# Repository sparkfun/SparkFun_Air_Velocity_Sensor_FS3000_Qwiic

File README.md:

SparkFun Air Velocity Sensor Breakout - FS3000 (Qwiic)
========================================

<table class="table table-hover table-striped table-bordered">
  <tr align="center">
   <td></td>
   <td></td>
  </tr>
  <tr align="center">
   <td><i>SparkFun Air Velocity Sensor Breakout <br /> FS3000-1005 (Qwiic) <br /> [ <a href="https://www.sparkfun.com/products/18377">SEN-18377</a> ]</i></td>
   <td><i>SparkFun Air Velocity Sensor Breakout <br /> FS3000-1015 (Qwiic) <br /> [ <a href="https://www.sparkfun.com/products/18768">SEN-18768</a> ]</i></td>
  </tr>
</table>

The SparkFun Air Velocity Sensor Breakout - FS3000 (Qwiic) makes it easy to use the Renesas FS3000 module. The FS3000 is a surface-mount type air velocity module utilizing a MEMS thermopile-based sensor. The FS3000 features a digital output with 12-bit resolution. The sensor comprises a "solid" thermal isolation technology and siliconcarbide coating to protect it from abrasive wear and water condensation. The FS3000 features a compact design fit for low profile enclosures.

There are two versions of this sensor with different upper ranges (1005/1015). This SparkFun product breaks out both versions on separate breakout boards: the 1005 version which can sense 0-7.23m/s (0-16.17mph) and 1015 version which can sense 0-15m/s (0-33.6mph).

SparkFun labored with love to create this code. Feel like supporting open source hardware?
Buy a [board](https://www.sparkfun.com/products/18377) or [two](https://www.sparkfun.com/products/18768) from SparkFun!

Repository Contents
-------------------

* **/Hardware** - Eagle design files (.brd, .sch)
* **/Hardware/Production** - Production panel files (.brd)
* **/Documents** - Datasheet, dimensional drawings.

Documentation
--------------

* **[Installing an Arduino Library Guide](https://learn.sparkfun.com/tutorials/installing-an-arduino-library)** - Basic information on how to install an Arduino library.
* **[Arduino Library](https://github.com/sparkfun/SparkFun_FS3000_Arduino_Library)** - Arduino Library for the Air Velocity Sensor FS3000.
* **[Hookup Guide](https://learn.sparkfun.com/tutorials/air-velocity-sensor-breakout---fs3000-hookup-guide)** - Hookup guide for the SparkFun Qwiic Air Velocity Sensor - FS3000.

Product Versions
----------------
* [SEN-18768](https://www.sparkfun.com/products/18768) - v1.0 with FS3000-1015
* [SEN-18377](https://www.sparkfun.com/products/18377) - v1.0 with FS3000-1005, Initial Release

License Information
-------------------

This product is _**open source**_! 

Please review the LICENSE.md file for license information. 

If you have any questions or concerns on licensing, please contact technical support on our [SparkFun forums](https://forum.sparkfun.com/viewforum.php?f=152).

Distributed as-is; no warranty is given.

- Your friends at SparkFun.

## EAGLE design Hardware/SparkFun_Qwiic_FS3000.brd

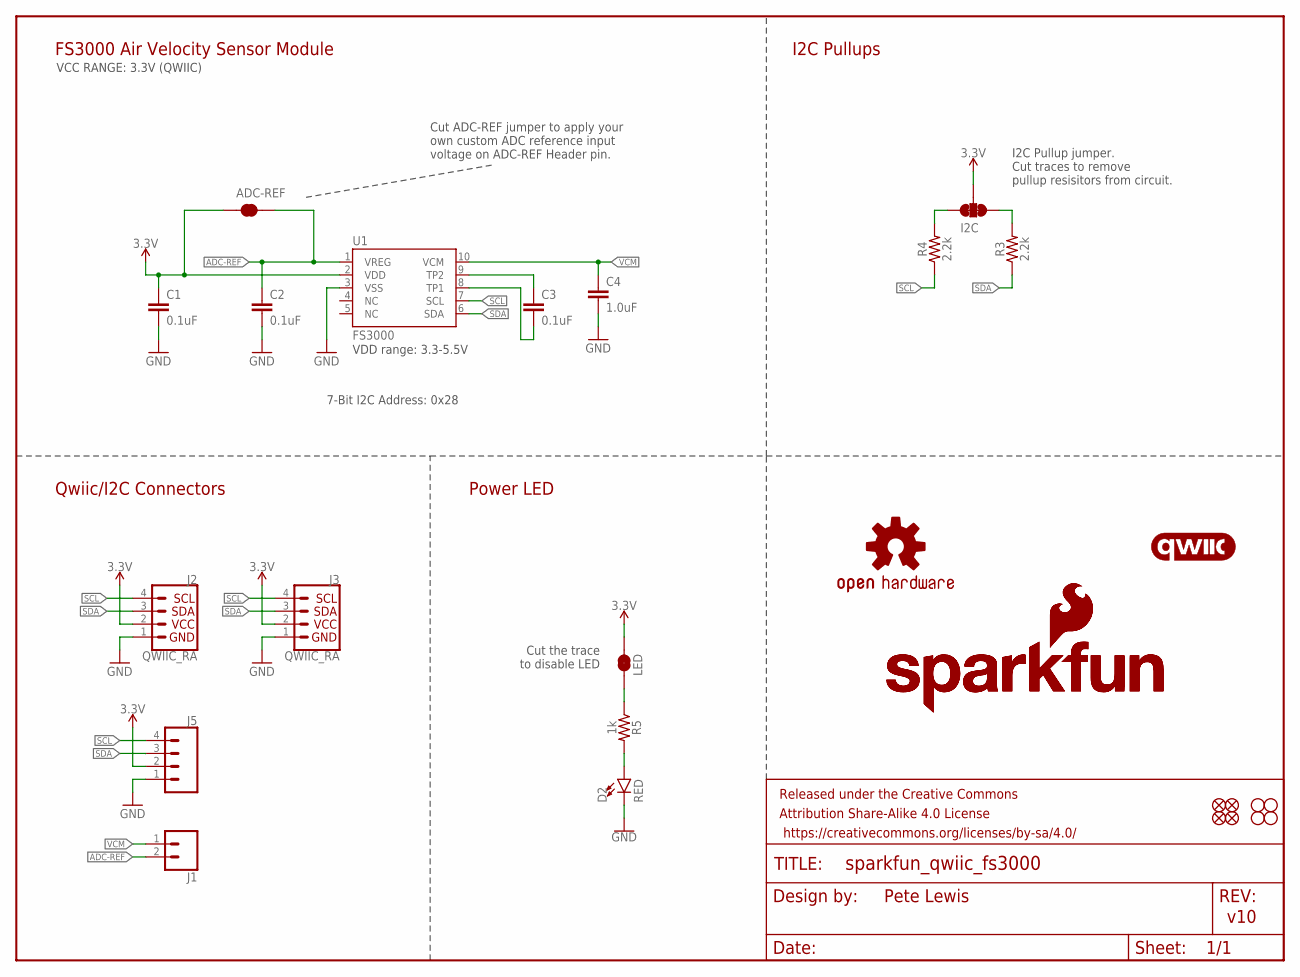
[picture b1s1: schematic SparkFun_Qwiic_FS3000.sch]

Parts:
ADC-REF: JUMPER-SMT_2_NC_TRACE_SILK; SMT-JUMPER_2_NC_TRACE_SILK
C1, C2, C3: 0.1uF; 0402-TIGHT
C4: 1.0uF; 0402-TIGHT
D2: RED; LED-0603
FRAME1: FRAME-LETTER; CREATIVE_COMMONS
I2C: JUMPER-SMT_3_2-NC_TRACE_SILK; SMT-JUMPER_3_2-NC_TRACE_SILK
J1: CONN_021X02_NO_SILK; 1X02_NO_SILK
J2, J3: QWIIC_RA; JST04_1MM_RA
J5: CONN_041X04_NO_SILK; 1X04_NO_SILK
JP1: LED; SMT-JUMPER_2_NC_TRACE_SILK
JP2, JP5, JP6, JP11: FIDUCIALUFIDUCIAL; FIDUCIAL-MICRO
JP3, JP4, JP7, JP8: STAND-OFF
LOGO1: OSHW-LOGOMINI; OSHW-LOGO-MINI
LOGO3, LOGO5: SFE_LOGO_NAME_FLAME.1_INCH; SFE_LOGO_NAME_FLAME_.1
LOGO4: QWIIC_LOGO_5MM; QWIIC_5MM
R3, R4: 2.2k; 0402-TIGHT
R5: 1k; 0402-TIGHT
U1: FS3000

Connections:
3.3V: ADC-REF.1, C1.1, I2C.2, J2.2, J3.2, J5.2, JP1.2, U1.2 (VDD)
ADC-REF: ADC-REF.2, C2.1, J1.2, U1.1 (VREG)
GND: C1.2, C2.2, C4.2, D2.C, J2.1, J3.1, J5.1, U1.3 (VSS)
unnamed: I2C.1, R3.2
unnamed: I2C.3, R4.2
unnamed: C3.1, U1.9 (TP2)
unnamed: C3.2, U1.8 (TP1)
unnamed: D2.A, R5.2
unnamed: JP1.1, R5.1
SCL: J2.4, J3.4, J5.4, R4.1, U1.7 (SCL)
SDA: J2.3, J3.3, J5.3, R3.1, U1.6 (SDA)
VCM: C4.1, J1.1, U1.10 (VCM)

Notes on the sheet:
7-Bit I2C Address: 0x28
Pete Lewis
v10
FS3000 Air Velocity Sensor Module
Qwiic/I2C Connectors
I2C Pullup jumper. Cut traces to remove pullup resisitors from circuit.
Cut the trace to disable LED
Power LED
VCC RANGE: 3.3V (QWIIC)
I2C Pullups
Cut ADC-REF jumper to apply your own custom ADC reference input voltage on ADC-REF Header pin.
VDD range: 3.3-5.5V

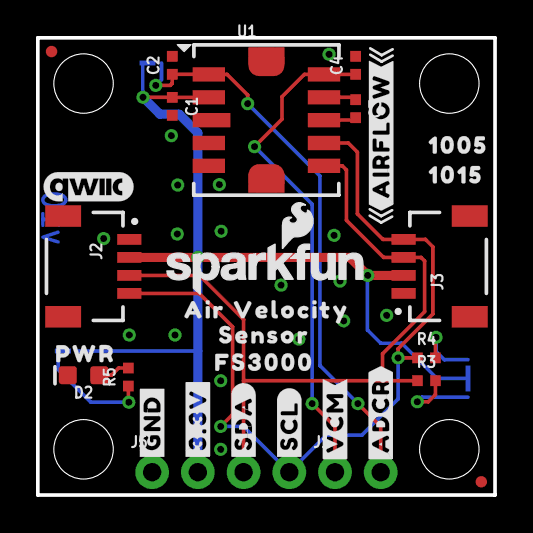
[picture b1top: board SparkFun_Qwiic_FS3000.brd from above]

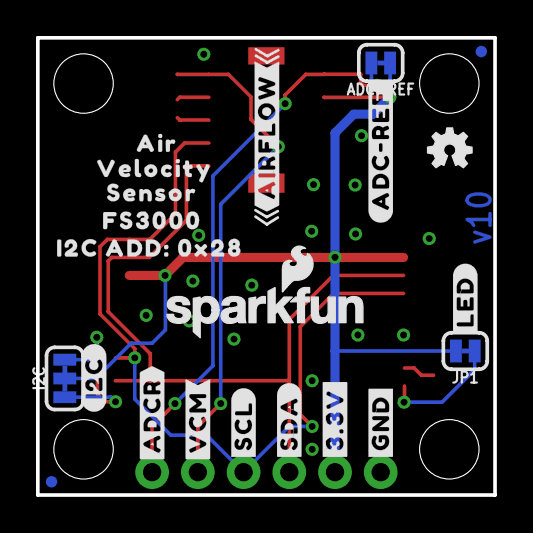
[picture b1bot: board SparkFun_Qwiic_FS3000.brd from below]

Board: 2 copper layers, 25.4 x 25.4 mm, 58 parts (22 on the bottom side), 12 nets.

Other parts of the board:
U$3, U$11: #SCL#0
U$4, U$9: #SDA#0
U$5, U$6: #GND#0
U$7, U$8: #3#3V#0
U$10, U$13: #ADCR#4
U$12: 10050
U$14, U$17: FS30001
U$15: #ADC#REF#0
U$16, U$20: VELOCITY30003
U$18, U$21: AIR30004
U$19, U$22: SENSOR30005
U$23, U$26: #AIRFLOW#0
U$24: #LED#0
U$25: PWR0
U$27: #I2C#0
U$28: I2C_ADD#_0X280
U$29: 10150
U$30, U$31: #VCM#3

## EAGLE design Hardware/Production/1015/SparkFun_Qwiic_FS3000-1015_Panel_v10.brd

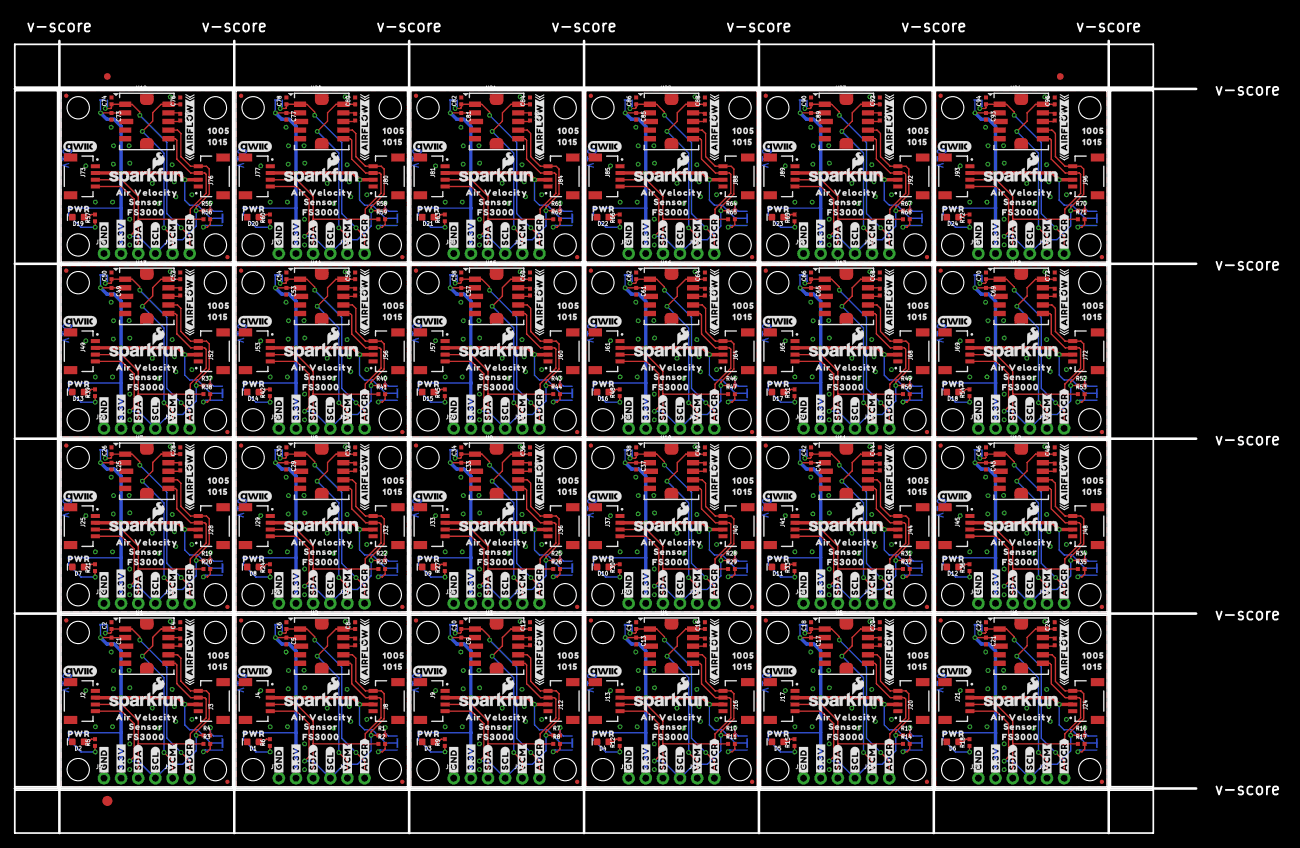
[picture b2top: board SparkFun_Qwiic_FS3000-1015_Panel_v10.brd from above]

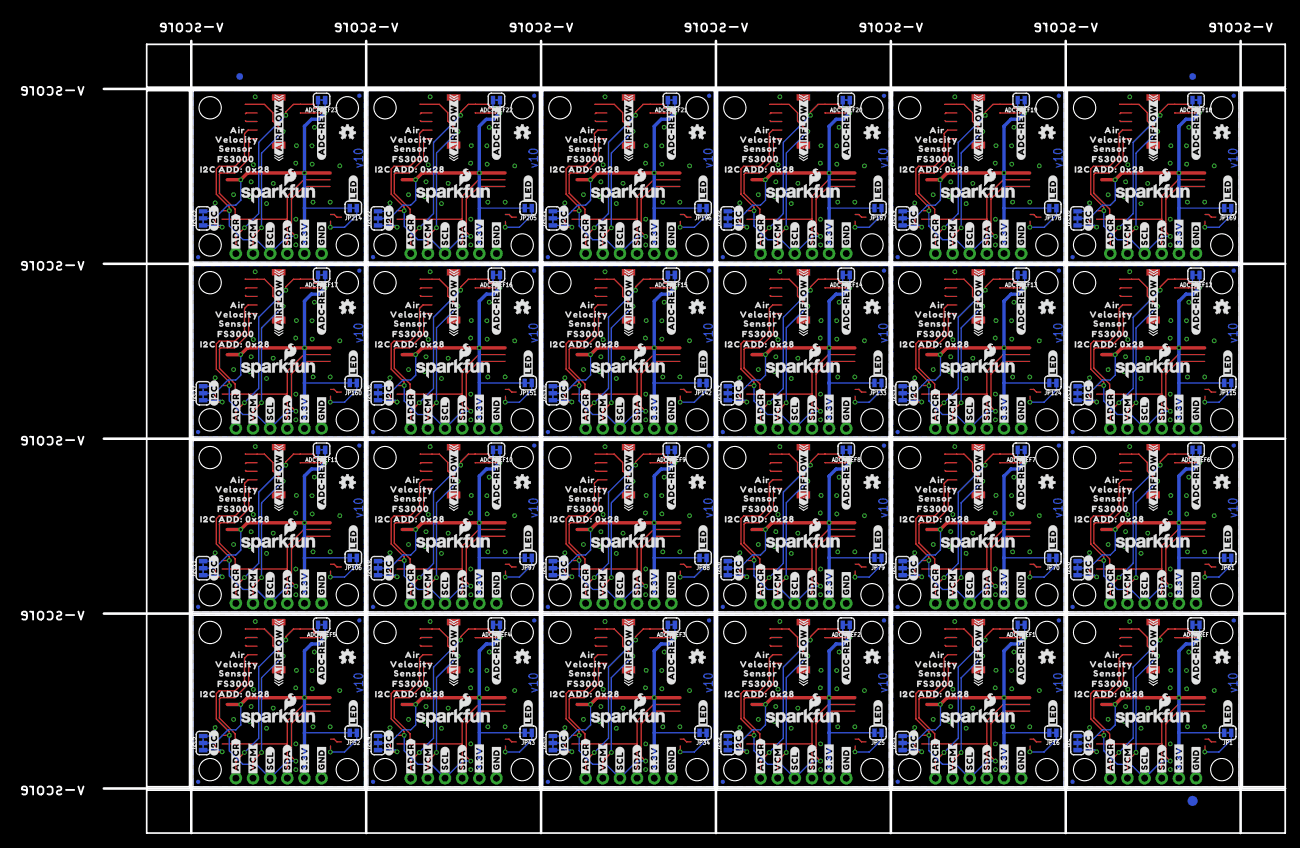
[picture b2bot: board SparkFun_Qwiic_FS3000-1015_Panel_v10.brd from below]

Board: 2 copper layers, 188.2 x 121.2 mm, 1374 parts (531 on the bottom side), 288 nets.

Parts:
ADC-REF, ADC-REF1, ADC-REF2, ADC-REF3, ADC-REF4, ADC-REF5, ADC-REF6, ADC-REF7, ADC-REF8, ADC-REF9, ADC-REF10, ADC-REF11, ADC-REF12, ADC-REF13, ADC-REF14, ADC-REF15, ADC-REF16, ADC-REF17, ADC-REF18, ADC-REF19, ADC-REF20, ADC-REF21, ADC-REF22, ADC-REF23: SMT-JUMPER_2_NC_TRACE_SILK
C1, C2, C3, C5, C6, C7, C9, C10, C11, C13, C14, C15, C17, C18, C19, C21, C22, C23, C25, C26, C27, C29, C30, C31, C33, C34, C35, C37, C38, C39, C41, C42, C43, C45, C46, C47, C49, C50, C51, C53, C54, C55, C57, C58, C59, C61, C62, C63, C65, C66, C67, C69, C70, C71, C73, C74, C75, C77, C78, C79, C81, C82, C83, C85, C86, C87, C89, C90, C91, C93, C94, C95: 0.1uF; 0402-TIGHT
C4, C8, C12, C16, C20, C24, C28, C32, C36, C40, C44, C48, C52, C56, C60, C64, C68, C72, C76, C80, C84, C88, C92, C96: 1.0uF; 0402-TIGHT
D1, D2, D3, D4, D5, D6, D7, D8, D9, D10, D11, D12, D13, D14, D15, D16, D17, D18, D19, D20, D21, D22, D23, D24: RED; LED-0603
E$1, E$2, E$3, E$4: FIDUCIAL-1X2
E$5, E$6: FIDUCIAL-1.5X3
I2C, I2C1, I2C2, I2C3, I2C4, I2C5, I2C6, I2C7, I2C8, I2C9, I2C10, I2C11, I2C12, I2C13, I2C14, I2C15, I2C16, I2C17, I2C18, I2C19, I2C20, I2C21, I2C22, I2C23: SMT-JUMPER_3_2-NC_TRACE_SILK
J1, J6, J10, J14, J18, J22, J26, J30, J34, J38, J42, J46, J50, J54, J58, J62, J66, J70, J74, J78, J82, J86, J90, J94: 1X02_NO_SILK
J2, J3, J4, J8, J9, J12, J13, J16, J17, J20, J21, J24, J25, J28, J29, J32, J33, J36, J37, J40, J41, J44, J45, J48, J49, J52, J53, J56, J57, J60, J61, J64, J65, J68, J69, J72, J73, J76, J77, J80, J81, J84, J85, J88, J89, J92, J93, J96: QWIIC_RA; JST04_1MM_RA
J5, J7, J11, J15, J19, J23, J27, J31, J35, J39, J43, J47, J51, J55, J59, J63, J67, J71, J75, J79, J83, J87, J91, J95: 1X04_NO_SILK
JP1, JP16, JP25, JP34, JP43, JP52, JP61, JP70, JP79, JP88, JP97, JP106, JP115, JP124, JP133, JP142, JP151, JP160, JP169, JP178, JP187, JP196, JP205, JP214: LED; SMT-JUMPER_2_NC_TRACE_SILK
JP2, JP5, JP6, JP10, JP11, JP12, JP13, JP14, JP20, JP21, JP22, JP23, JP29, JP30, JP31, JP32, JP38, JP39, JP40, JP41, JP47, JP48, JP49, JP50, JP56, JP57, JP58, JP59, JP65, JP66, JP67, JP68, JP74, JP75, JP76, JP77, JP83, JP84, JP85, JP86, JP92, JP93, JP94, JP95, JP101, JP102, JP103, JP104, JP110, JP111, JP112, JP113, JP119, JP120, JP121, JP122, JP128, JP129, JP130, JP131, JP137, JP138, JP139, JP140, JP146, JP147, JP148, JP149, JP155, JP156, JP157, JP158, JP164, JP165, JP166, JP167, JP173, JP174, JP175, JP176, JP182, JP183, JP184, JP185, JP191, JP192, JP193, JP194, JP200, JP201, JP202, JP203, JP209, JP210, JP211, JP212: FIDUCIALUFIDUCIAL; FIDUCIAL-MICRO
JP3, JP4, JP7, JP8, JP9, JP15, JP17, JP18, JP19, JP24, JP26, JP27, JP28, JP33, JP35, JP36, JP37, JP42, JP44, JP45, JP46, JP51, JP53, JP54, JP55, JP60, JP62, JP63, JP64, JP69, JP71, JP72, JP73, JP78, JP80, JP81, JP82, JP87, JP89, JP90, JP91, JP96, JP98, JP99, JP100, JP105, JP107, JP108, JP109, JP114, JP116, JP117, JP118, JP123, JP125, JP126, JP127, JP132, JP134, JP135, JP136, JP141, JP143, JP144, JP145, JP150, JP152, JP153, JP154, JP159, JP161, JP162, JP163, JP168, JP170, JP171, JP172, JP177, JP179, JP180, JP181, JP186, JP188, JP189, JP190, JP195, JP197, JP198, JP199, JP204, JP206, JP207, JP208, JP213, JP215, JP216: STAND-OFF
LOGO1, LOGO2, LOGO9, LOGO13, LOGO17, LOGO21, LOGO25, LOGO29, LOGO33, LOGO37, LOGO41, LOGO45, LOGO49, LOGO53, LOGO57, LOGO61, LOGO65, LOGO69, LOGO73, LOGO77, LOGO81, LOGO85, LOGO89, LOGO93: OSHW-LOGOMINI; OSHW-LOGO-MINI
LOGO3, LOGO5, LOGO7, LOGO8, LOGO11, LOGO12, LOGO15, LOGO16, LOGO19, LOGO20, LOGO23, LOGO24, LOGO27, LOGO28, LOGO31, LOGO32, LOGO35, LOGO36, LOGO39, LOGO40, LOGO43, LOGO44, LOGO47, LOGO48, LOGO51, LOGO52, LOGO55, LOGO56, LOGO59, LOGO60, LOGO63, LOGO64, LOGO67, LOGO68, LOGO71, LOGO72, LOGO75, LOGO76, LOGO79, LOGO80, LOGO83, LOGO84, LOGO87, LOGO88, LOGO91, LOGO92, LOGO95, LOGO96: SFE_LOGO_NAME_FLAME.1_INCH; SFE_LOGO_NAME_FLAME_.1
LOGO4, LOGO6, LOGO10, LOGO14, LOGO18, LOGO22, LOGO26, LOGO30, LOGO34, LOGO38, LOGO42, LOGO46, LOGO50, LOGO54, LOGO58, LOGO62, LOGO66, LOGO70, LOGO74, LOGO78, LOGO82, LOGO86, LOGO90, LOGO94: QWIIC_LOGO_5MM; QWIIC_5MM
R1, R2, R3, R4, R7, R8, R10, R11, R13, R14, R16, R17, R19, R20, R22, R23, R25, R26, R28, R29, R31, R32, R34, R35, R37, R38, R40, R41, R43, R44, R46, R47, R49, R50, R52, R53, R55, R56, R58, R59, R61, R62, R64, R65, R67, R68, R70, R71: 2.2k; 0402-TIGHT
R5, R6, R9, R12, R15, R18, R21, R24, R27, R30, R33, R36, R39, R42, R45, R48, R51, R54, R57, R60, R63, R66, R69, R72: 1k; 0402-TIGHT
U1, U2, U3, U4, U5, U6, U7, U8, U9, U10, U11, U12, U13, U14, U15, U16, U17, U18, U19, U20, U21, U22, U23, U24: FS3000
U$1, U$2, U$5, U$6, U$59, U$60, U$88, U$89, U$117, U$118, U$146, U$147, U$175, U$176, U$204, U$205, U$233, U$234, U$262, U$263, U$291, U$292, U$320, U$321, U$349, U$350, U$378, U$379, U$407, U$408, U$436, U$437, U$465, U$466, U$494, U$495, U$523, U$524, U$552, U$553, U$581, U$582, U$610, U$611, U$639, U$640, U$668, U$669: #GND#0
U$3, U$11, U$35, U$39, U$64, U$68, U$93, U$97, U$122, U$126, U$151, U$155, U$180, U$184, U$209, U$213, U$238, U$242, U$267, U$271, U$296, U$300, U$325, U$329, U$354, U$358, U$383, U$387, U$412, U$416, U$441, U$445, U$470, U$474, U$499, U$503, U$528, U$532, U$557, U$561, U$586, U$590, U$615, U$619, U$644, U$648, U$673, U$677: #SCL#0
U$4, U$9, U$34, U$40, U$63, U$69, U$92, U$98, U$121, U$127, U$150, U$156, U$179, U$185, U$208, U$214, U$237, U$243, U$266, U$272, U$295, U$301, U$324, U$330, U$353, U$359, U$382, U$388, U$411, U$417, U$440, U$446, U$469, U$475, U$498, U$504, U$527, U$533, U$556, U$562, U$585, U$591, U$614, U$620, U$643, U$649, U$672, U$678: #SDA#0
U$7, U$8, U$32, U$33, U$61, U$62, U$90, U$91, U$119, U$120, U$148, U$149, U$177, U$178, U$206, U$207, U$235, U$236, U$264, U$265, U$293, U$294, U$322, U$323, U$351, U$352, U$380, U$381, U$409, U$410, U$438, U$439, U$467, U$468, U$496, U$497, U$525, U$526, U$554, U$555, U$583, U$584, U$612, U$613, U$641, U$642, U$670, U$671: #3#3V#0
U$10, U$13, U$55, U$56, U$84, U$85, U$113, U$114, U$142, U$143, U$171, U$172, U$200, U$201, U$229, U$230, U$258, U$259, U$287, U$288, U$316, U$317, U$345, U$346, U$374, U$375, U$403, U$404, U$432, U$433, U$461, U$462, U$490, U$491, U$519, U$520, U$548, U$549, U$577, U$578, U$606, U$607, U$635, U$636, U$664, U$665, U$693, U$694: #ADCR#4
U$12, U$53, U$82, U$111, U$140, U$169, U$198, U$227, U$256, U$285, U$314, U$343, U$372, U$401, U$430, U$459, U$488, U$517, U$546, U$575, U$604, U$633, U$662, U$691: 10050
U$14, U$17, U$41, U$46, U$70, U$75, U$99, U$104, U$128, U$133, U$157, U$162, U$186, U$191, U$215, U$220, U$244, U$249, U$273, U$278, U$302, U$307, U$331, U$336, U$360, U$365, U$389, U$394, U$418, U$423, U$447, U$452, U$476, U$481, U$505, U$510, U$534, U$539, U$563, U$568, U$592, U$597, U$621, U$626, U$650, U$655, U$679, U$684: FS30001
U$15, U$45, U$74, U$103, U$132, U$161, U$190, U$219, U$248, U$277, U$306, U$335, U$364, U$393, U$422, U$451, U$480, U$509, U$538, U$567, U$596, U$625, U$654, U$683: #ADC#REF#0
U$16, U$20, U$42, U$47, U$71, U$76, U$100, U$105, U$129, U$134, U$158, U$163, U$187, U$192, U$216, U$221, U$245, U$250, U$274, U$279, U$303, U$308, U$332, U$337, U$361, U$366, U$390, U$395, U$419, U$424, U$448, U$453, U$477, U$482, U$506, U$511, U$535, U$540, U$564, U$569, U$593, U$598, U$622, U$627, U$651, U$656, U$680, U$685: VELOCITY30003
U$18, U$21, U$43, U$48, U$72, U$77, U$101, U$106, U$130, U$135, U$159, U$164, U$188, U$193, U$217, U$222, U$246, U$251, U$275, U$280, U$304, U$309, U$333, U$338, U$362, U$367, U$391, U$396, U$420, U$425, U$449, U$454, U$478, U$483, U$507, U$512, U$536, U$541, U$565, U$570, U$594, U$599, U$623, U$628, U$652, U$657, U$681, U$686: AIR30004
U$19, U$22, U$44, U$49, U$73, U$78, U$102, U$107, U$131, U$136, U$160, U$165, U$189, U$194, U$218, U$223, U$247, U$252, U$276, U$281, U$305, U$310, U$334, U$339, U$363, U$368, U$392, U$397, U$421, U$426, U$450, U$455, U$479, U$484, U$508, U$513, U$537, U$542, U$566, U$571, U$595, U$600, U$624, U$629, U$653, U$658, U$682, U$687: SENSOR30005
U$23, U$26, U$50, U$51, U$79, U$80, U$108, U$109, U$137, U$138, U$166, U$167, U$195, U$196, U$224, U$225, U$253, U$254, U$282, U$283, U$311, U$312, U$340, U$341, U$369, U$370, U$398, U$399, U$427, U$428, U$456, U$457, U$485, U$486, U$514, U$515, U$543, U$544, U$572, U$573, U$601, U$602, U$630, U$631, U$659, U$660, U$688, U$689: #AIRFLOW#0
U$24, U$36, U$65, U$94, U$123, U$152, U$181, U$210, U$239, U$268, U$297, U$326, U$355, U$384, U$413, U$442, U$471, U$500, U$529, U$558, U$587, U$616, U$645, U$674: #LED#0
U$25, U$37, U$66, U$95, U$124, U$153, U$182, U$211, U$240, U$269, U$298, U$327, U$356, U$385, U$414, U$443, U$472, U$501, U$530, U$559, U$588, U$617, U$646, U$675: PWR0
U$27, U$38, U$67, U$96, U$125, U$154, U$183, U$212, U$241, U$270, U$299, U$328, U$357, U$386, U$415, U$444, U$473, U$502, U$531, U$560, U$589, U$618, U$647, U$676: #I2C#0
U$28, U$52, U$81, U$110, U$139, U$168, U$197, U$226, U$255, U$284, U$313, U$342, U$371, U$400, U$429, U$458, U$487, U$516, U$545, U$574, U$603, U$632, U$661, U$690: I2C_ADD#_0X280
U$29, U$54, U$83, U$112, U$141, U$170, U$199, U$228, U$257, U$286, U$315, U$344, U$373, U$402, U$431, U$460, U$489, U$518, U$547, U$576, U$605, U$634, U$663, U$692: 10150
U$30, U$31, U$57, U$58, U$86, U$87, U$115, U$116, U$144, U$145, U$173, U$174, U$202, U$203, U$231, U$232, U$260, U$261, U$289, U$290, U$318, U$319, U$347, U$348, U$376, U$377, U$405, U$406, U$434, U$435, U$463, U$464, U$492, U$493, U$521, U$522, U$550, U$551, U$579, U$580, U$608, U$609, U$637, U$638, U$666, U$667, U$695, U$696: #VCM#3

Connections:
3.3V: ADC-REF.1, C1.1, I2C.2, J2.2, J3.2, J5.2, JP1.2, U1.2
3.3V1: ADC-REF1.1, C5.1, I2C1.2, J4.2, J7.2, J8.2, JP16.2, U2.2
3.3V2: ADC-REF2.1, C9.1, I2C2.2, J9.2, J11.2, J12.2, JP25.2, U3.2
3.3V3: ADC-REF3.1, C13.1, I2C3.2, J13.2, J15.2, J16.2, JP34.2, U4.2
3.3V4: ADC-REF4.1, C17.1, I2C4.2, J17.2, J19.2, J20.2, JP43.2, U5.2
3.3V5: ADC-REF5.1, C21.1, I2C5.2, J21.2, J23.2, J24.2, JP52.2, U6.2
3.3V6: ADC-REF6.1, C25.1, I2C6.2, J25.2, J27.2, J28.2, JP61.2, U7.2
3.3V7: ADC-REF7.1, C29.1, I2C7.2, J29.2, J31.2, J32.2, JP70.2, U8.2
3.3V8: ADC-REF8.1, C33.1, I2C8.2, J33.2, J35.2, J36.2, JP79.2, U9.2
3.3V9: ADC-REF9.1, C37.1, I2C9.2, J37.2, J39.2, J40.2, JP88.2, U10.2
3.3V10: ADC-REF10.1, C41.1, I2C10.2, J41.2, J43.2, J44.2, JP97.2, U11.2
3.3V11: ADC-REF11.1, C45.1, I2C11.2, J45.2, J47.2, J48.2, JP106.2, U12.2
3.3V12: ADC-REF12.1, C49.1, I2C12.2, J49.2, J51.2, J52.2, JP115.2, U13.2
3.3V13: ADC-REF13.1, C53.1, I2C13.2, J53.2, J55.2, J56.2, JP124.2, U14.2
3.3V14: ADC-REF14.1, C57.1, I2C14.2, J57.2, J59.2, J60.2, JP133.2, U15.2
3.3V15: ADC-REF15.1, C61.1, I2C15.2, J61.2, J63.2, J64.2, JP142.2, U16.2
3.3V16: ADC-REF16.1, C65.1, I2C16.2, J65.2, J67.2, J68.2, JP151.2, U17.2
3.3V17: ADC-REF17.1, C69.1, I2C17.2, J69.2, J71.2, J72.2, JP160.2, U18.2
3.3V18: ADC-REF18.1, C73.1, I2C18.2, J73.2, J75.2, J76.2, JP169.2, U19.2
3.3V19: ADC-REF19.1, C77.1, I2C19.2, J77.2, J79.2, J80.2, JP178.2, U20.2
3.3V20: ADC-REF20.1, C81.1, I2C20.2, J81.2, J83.2, J84.2, JP187.2, U21.2
3.3V21: ADC-REF21.1, C85.1, I2C21.2, J85.2, J87.2, J88.2, JP196.2, U22.2
3.3V22: ADC-REF22.1, C89.1, I2C22.2, J89.2, J91.2, J92.2, JP205.2, U23.2
3.3V23: ADC-REF23.1, C93.1, I2C23.2, J93.2, J95.2, J96.2, JP214.2, U24.2
ADC-REF: ADC-REF.2, C2.1, J1.2, U1.1
ADC-REF1: ADC-REF1.2, C6.1, J6.2, U2.1
ADC-REF2: ADC-REF2.2, C10.1, J10.2, U3.1
ADC-REF3: ADC-REF3.2, C14.1, J14.2, U4.1
ADC-REF4: ADC-REF4.2, C18.1, J18.2, U5.1
ADC-REF5: ADC-REF5.2, C22.1, J22.2, U6.1
ADC-REF6: ADC-REF6.2, C26.1, J26.2, U7.1
ADC-REF7: ADC-REF7.2, C30.1, J30.2, U8.1
ADC-REF8: ADC-REF8.2, C34.1, J34.2, U9.1
ADC-REF9: ADC-REF9.2, C38.1, J38.2, U10.1
ADC-REF10: ADC-REF10.2, C42.1, J42.2, U11.1
ADC-REF11: ADC-REF11.2, C46.1, J46.2, U12.1
ADC-REF12: ADC-REF12.2, C50.1, J50.2, U13.1
ADC-REF13: ADC-REF13.2, C54.1, J54.2, U14.1
ADC-REF14: ADC-REF14.2, C58.1, J58.2, U15.1
ADC-REF15: ADC-REF15.2, C62.1, J62.2, U16.1
ADC-REF16: ADC-REF16.2, C66.1, J66.2, U17.1
ADC-REF17: ADC-REF17.2, C70.1, J70.2, U18.1
ADC-REF18: ADC-REF18.2, C74.1, J74.2, U19.1
ADC-REF19: ADC-REF19.2, C78.1, J78.2, U20.1
ADC-REF20: ADC-REF20.2, C82.1, J82.2, U21.1
ADC-REF21: ADC-REF21.2, C86.1, J86.2, U22.1
ADC-REF22: ADC-REF22.2, C90.1, J90.2, U23.1
ADC-REF23: ADC-REF23.2, C94.1, J94.2, U24.1
GND: C1.2, C2.2, C4.2, D2.C, J2.1, J3.1, J5.1, U1.3
GND1: C5.2, C6.2, C8.2, D1.C, J4.1, J7.1, J8.1, U2.3
GND2: C9.2, C10.2, C12.2, D3.C, J9.1, J11.1, J12.1, U3.3
GND3: C13.2, C14.2, C16.2, D4.C, J13.1, J15.1, J16.1, U4.3
GND4: C17.2, C18.2, C20.2, D5.C, J17.1, J19.1, J20.1, U5.3
GND5: C21.2, C22.2, C24.2, D6.C, J21.1, J23.1, J24.1, U6.3
GND6: C25.2, C26.2, C28.2, D7.C, J25.1, J27.1, J28.1, U7.3
GND7: C29.2, C30.2, C32.2, D8.C, J29.1, J31.1, J32.1, U8.3
GND8: C33.2, C34.2, C36.2, D9.C, J33.1, J35.1, J36.1, U9.3
GND9: C37.2, C38.2, C40.2, D10.C, J37.1, J39.1, J40.1, U10.3
GND10: C41.2, C42.2, C44.2, D11.C, J41.1, J43.1, J44.1, U11.3
GND11: C45.2, C46.2, C48.2, D12.C, J45.1, J47.1, J48.1, U12.3
GND12: C49.2, C50.2, C52.2, D13.C, J49.1, J51.1, J52.1, U13.3
GND13: C53.2, C54.2, C56.2, D14.C, J53.1, J55.1, J56.1, U14.3
GND14: C57.2, C58.2, C60.2, D15.C, J57.1, J59.1, J60.1, U15.3
GND15: C61.2, C62.2, C64.2, D16.C, J61.1, J63.1, J64.1, U16.3
GND16: C65.2, C66.2, C68.2, D17.C, J65.1, J67.1, J68.1, U17.3
GND17: C69.2, C70.2, C72.2, D18.C, J69.1, J71.1, J72.1, U18.3
GND18: C73.2, C74.2, C76.2, D19.C, J73.1, J75.1, J76.1, U19.3
GND19: C77.2, C78.2, C80.2, D20.C, J77.1, J79.1, J80.1, U20.3
GND20: C81.2, C82.2, C84.2, D21.C, J81.1, J83.1, J84.1, U21.3
GND21: C85.2, C86.2, C88.2, D22.C, J85.1, J87.1, J88.1, U22.3
GND22: C89.2, C90.2, C92.2, D23.C, J89.1, J91.1, J92.1, U23.3
GND23: C93.2, C94.2, C96.2, D24.C, J93.1, J95.1, J96.1, U24.3
unnamed: I2C.1, R3.2
unnamed: I2C.3, R4.2
unnamed: C3.1, U1.9
unnamed: C3.2, U1.8
unnamed: I2C1.1, R2.2
unnamed: D2.A, R5.2
unnamed: I2C1.3, R1.2
unnamed: JP1.1, R5.1
unnamed: D1.A, R6.2
unnamed: JP16.1, R6.1
unnamed: C7.1, U2.9
unnamed: C7.2, U2.8
unnamed: I2C2.1, R8.2
unnamed: I2C2.3, R7.2
unnamed: D3.A, R9.2
unnamed: JP25.1, R9.1
unnamed: C11.1, U3.9
unnamed: C11.2, U3.8
unnamed: I2C3.1, R11.2
unnamed: I2C3.3, R10.2
unnamed: D4.A, R12.2
unnamed: JP34.1, R12.1
unnamed: C15.1, U4.9
unnamed: C15.2, U4.8
unnamed: I2C4.1, R14.2
unnamed: I2C4.3, R13.2
unnamed: D5.A, R15.2
unnamed: JP43.1, R15.1
unnamed: C19.1, U5.9
unnamed: C19.2, U5.8
unnamed: I2C5.1, R17.2
unnamed: I2C5.3, R16.2
unnamed: D6.A, R18.2
unnamed: JP52.1, R18.1
unnamed: C23.1, U6.9
unnamed: C23.2, U6.8
unnamed: I2C6.1, R20.2
unnamed: I2C6.3, R19.2
unnamed: D7.A, R21.2
unnamed: JP61.1, R21.1
unnamed: C27.1, U7.9
unnamed: C27.2, U7.8
unnamed: I2C7.1, R23.2
unnamed: I2C7.3, R22.2
unnamed: D8.A, R24.2
unnamed: JP70.1, R24.1
unnamed: C31.1, U8.9
unnamed: C31.2, U8.8
unnamed: I2C8.1, R26.2
unnamed: I2C8.3, R25.2
unnamed: D9.A, R27.2
unnamed: JP79.1, R27.1
unnamed: C35.1, U9.9
unnamed: C35.2, U9.8
unnamed: I2C9.1, R29.2
unnamed: I2C9.3, R28.2
unnamed: D10.A, R30.2
unnamed: JP88.1, R30.1
unnamed: C39.1, U10.9
unnamed: C39.2, U10.8
unnamed: I2C10.1, R32.2
unnamed: I2C10.3, R31.2
unnamed: D11.A, R33.2
unnamed: JP97.1, R33.1
unnamed: C43.1, U11.9
unnamed: C43.2, U11.8
unnamed: I2C11.1, R35.2
unnamed: I2C11.3, R34.2
unnamed: D12.A, R36.2
unnamed: JP106.1, R36.1
unnamed: C47.1, U12.9
unnamed: C47.2, U12.8
unnamed: I2C12.1, R38.2
unnamed: I2C12.3, R37.2
unnamed: D13.A, R39.2
unnamed: JP115.1, R39.1
unnamed: C51.1, U13.9
unnamed: C51.2, U13.8
unnamed: I2C13.1, R41.2
unnamed: I2C13.3, R40.2
unnamed: D14.A, R42.2
unnamed: JP124.1, R42.1
unnamed: C55.1, U14.9
unnamed: C55.2, U14.8
unnamed: I2C14.1, R44.2
unnamed: I2C14.3, R43.2
unnamed: D15.A, R45.2
unnamed: JP133.1, R45.1
unnamed: C59.1, U15.9
unnamed: C59.2, U15.8
unnamed: I2C15.1, R47.2
unnamed: I2C15.3, R46.2
unnamed: D16.A, R48.2
unnamed: JP142.1, R48.1
unnamed: C63.1, U16.9
unnamed: C63.2, U16.8
unnamed: I2C16.1, R50.2
unnamed: I2C16.3, R49.2
unnamed: D17.A, R51.2
unnamed: JP151.1, R51.1
unnamed: C67.1, U17.9
unnamed: C67.2, U17.8
unnamed: I2C17.1, R53.2
unnamed: I2C17.3, R52.2
unnamed: D18.A, R54.2
unnamed: JP160.1, R54.1
unnamed: C71.1, U18.9
unnamed: C71.2, U18.8
unnamed: I2C18.1, R56.2
unnamed: I2C18.3, R55.2
unnamed: D19.A, R57.2
unnamed: JP169.1, R57.1
unnamed: C75.1, U19.9
unnamed: C75.2, U19.8
unnamed: I2C19.1, R59.2
unnamed: I2C19.3, R58.2
unnamed: D20.A, R60.2
unnamed: JP178.1, R60.1
unnamed: C79.1, U20.9
unnamed: C79.2, U20.8
unnamed: I2C20.1, R62.2
unnamed: I2C20.3, R61.2
unnamed: D21.A, R63.2
unnamed: JP187.1, R63.1
unnamed: C83.1, U21.9
unnamed: C83.2, U21.8
unnamed: I2C21.1, R65.2
unnamed: I2C21.3, R64.2
unnamed: D22.A, R66.2
unnamed: JP196.1, R66.1
unnamed: C87.1, U22.9
unnamed: C87.2, U22.8
unnamed: I2C22.1, R68.2
unnamed: I2C22.3, R67.2
unnamed: D23.A, R69.2
unnamed: JP205.1, R69.1
unnamed: C91.1, U23.9
unnamed: C91.2, U23.8
unnamed: I2C23.1, R71.2
unnamed: I2C23.3, R70.2
unnamed: D24.A, R72.2
unnamed: JP214.1, R72.1
unnamed: C95.1, U24.9
unnamed: C95.2, U24.8
SCL: J2.4, J3.4, J5.4, R4.1, U1.7
SCL1: J4.4, J7.4, J8.4, R1.1, U2.7
SCL2: J9.4, J11.4, J12.4, R7.1, U3.7
SCL3: J13.4, J15.4, J16.4, R10.1, U4.7
SCL4: J17.4, J19.4, J20.4, R13.1, U5.7
SCL5: J21.4, J23.4, J24.4, R16.1, U6.7
SCL6: J25.4, J27.4, J28.4, R19.1, U7.7
SCL7: J29.4, J31.4, J32.4, R22.1, U8.7
SCL8: J33.4, J35.4, J36.4, R25.1, U9.7
SCL9: J37.4, J39.4, J40.4, R28.1, U10.7
SCL10: J41.4, J43.4, J44.4, R31.1, U11.7
SCL11: J45.4, J47.4, J48.4, R34.1, U12.7
SCL12: J49.4, J51.4, J52.4, R37.1, U13.7
SCL13: J53.4, J55.4, J56.4, R40.1, U14.7
SCL14: J57.4, J59.4, J60.4, R43.1, U15.7
SCL15: J61.4, J63.4, J64.4, R46.1, U16.7
SCL16: J65.4, J67.4, J68.4, R49.1, U17.7
SCL17: J69.4, J71.4, J72.4, R52.1, U18.7
SCL18: J73.4, J75.4, J76.4, R55.1, U19.7
SCL19: J77.4, J79.4, J80.4, R58.1, U20.7
SCL20: J81.4, J83.4, J84.4, R61.1, U21.7
SCL21: J85.4, J87.4, J88.4, R64.1, U22.7
SCL22: J89.4, J91.4, J92.4, R67.1, U23.7
SCL23: J93.4, J95.4, J96.4, R70.1, U24.7
SDA: J2.3, J3.3, J5.3, R3.1, U1.6
SDA1: J4.3, J7.3, J8.3, R2.1, U2.6
SDA2: J9.3, J11.3, J12.3, R8.1, U3.6
SDA3: J13.3, J15.3, J16.3, R11.1, U4.6
SDA4: J17.3, J19.3, J20.3, R14.1, U5.6
SDA5: J21.3, J23.3, J24.3, R17.1, U6.6
SDA6: J25.3, J27.3, J28.3, R20.1, U7.6
SDA7: J29.3, J31.3, J32.3, R23.1, U8.6
SDA8: J33.3, J35.3, J36.3, R26.1, U9.6
SDA9: J37.3, J39.3, J40.3, R29.1, U10.6
SDA10: J41.3, J43.3, J44.3, R32.1, U11.6
SDA11: J45.3, J47.3, J48.3, R35.1, U12.6
SDA12: J49.3, J51.3, J52.3, R38.1, U13.6
SDA13: J53.3, J55.3, J56.3, R41.1, U14.6
SDA14: J57.3, J59.3, J60.3, R44.1, U15.6
SDA15: J61.3, J63.3, J64.3, R47.1, U16.6
SDA16: J65.3, J67.3, J68.3, R50.1, U17.6
SDA17: J69.3, J71.3, J72.3, R53.1, U18.6
SDA18: J73.3, J75.3, J76.3, R56.1, U19.6
SDA19: J77.3, J79.3, J80.3, R59.1, U20.6
SDA20: J81.3, J83.3, J84.3, R62.1, U21.6
SDA21: J85.3, J87.3, J88.3, R65.1, U22.6
SDA22: J89.3, J91.3, J92.3, R68.1, U23.6
SDA23: J93.3, J95.3, J96.3, R71.1, U24.6
VCM: C4.1, J1.1, U1.10
VCM1: C8.1, J6.1, U2.10
VCM2: C12.1, J10.1, U3.10
VCM3: C16.1, J14.1, U4.10
VCM4: C20.1, J18.1, U5.10
VCM5: C24.1, J22.1, U6.10
VCM6: C28.1, J26.1, U7.10
VCM7: C32.1, J30.1, U8.10
VCM8: C36.1, J34.1, U9.10
VCM9: C40.1, J38.1, U10.10
VCM10: C44.1, J42.1, U11.10
VCM11: C48.1, J46.1, U12.10
VCM12: C52.1, J50.1, U13.10
VCM13: C56.1, J54.1, U14.10
VCM14: C60.1, J58.1, U15.10
VCM15: C64.1, J62.1, U16.10
VCM16: C68.1, J66.1, U17.10
VCM17: C72.1, J70.1, U18.10
VCM18: C76.1, J74.1, U19.10
VCM19: C80.1, J78.1, U20.10
VCM20: C84.1, J82.1, U21.10
VCM21: C88.1, J86.1, U22.10
VCM22: C92.1, J90.1, U23.10
VCM23: C96.1, J94.1, U24.10

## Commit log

2021-06-17 Initial layout started
2021-06-17 Layout done
2021-06-17 ran checklist pre-group review
    -DRC update
    -measures update
    -paste reduced on IC pads
2021-06-18 created alternate option with sensor at "top" edge of PCB
2021-06-18 manufacturing tab color changed to red, proto pic updated to show both options
2021-06-18 Group Review Changes
    -Buzzard labels on VCM/ADCR changed to be correct inputs/outputs end type
    -Added in solder pads for two versions (7.23m/s vs 15m/s) (1005/1015)
    -Moved"supply range" to below the IC and change to "VDD range".
    -schematic cleanup - power LED jumper paragraph. space in I2C address.
    -added space between "I2C address" and "0x28" in board silk
    -added name/flame logo to board silk.
2021-06-18 Renaming and reorganizing to "TEE" and "1X1"
    Going to prototype with both designs to determine if TEE shape has better/different performance.
2021-06-21 eng ran checklist before double-check request
    -dimensions were off grid slightly, corrected [1X1 version].
    -approved DRC overlap error on jumper [1X1 version].
    -added a couple more stitching GND vias [1X1]
    -updated pad 3 to extend longer as shown in datasheet [both versions]
2021-06-21 updated some stuff to correct recent libraries
    -GNDs, Fiducials, and standoffs were still in old library. updated.
2021-06-22 Proto panel and gerbers
    -Made a proto panel that includes 3 copies of each design. This allows us to order a single stencil and saves production time when building 3 prototype copies of each (1X1 and TEE) by hand.
    -note, I had to move the VCM and ADCR buzzard labels on the 1x1 to a separate library, so I could drop it into the "proto panel" without it updating/breaking the other design.
2021-06-23 re-panelized proto to meet 70cm width requirement for V-Scores
2021-06-24 Removed leftover tStop/tCream for IC type on 1X1s
2021-08-13 Decided to use 1X1 version, bumped version to "v10"
2021-08-16 version jumper switched to complete rectangle pad w/paste
2021-08-16 production panel v10b
2021-09-10 readme image and dimensions
2021-10-14 Gerbers for 1015 version that include GTP blob for 1015 pad/version
    Note, I just copied the panel file and shifted the tCream rectangles so they line up with the rectangle mask openings next to the 1015 silk text.
2022-10-03 Update Datasheet

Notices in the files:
parts and their libraries:
SparkFun-Resistors: Licensing: Creative Commons ShareAlike 4.0 International - https://creativecommons.org/licenses/by-sa/4.0
SparkFun-Aesthetics: Released under the Creative Commons Attribution Share-Alike 4.0 License
SparkFun-Aesthetics: https://creativecommons.org/licenses/by-sa/4.0
